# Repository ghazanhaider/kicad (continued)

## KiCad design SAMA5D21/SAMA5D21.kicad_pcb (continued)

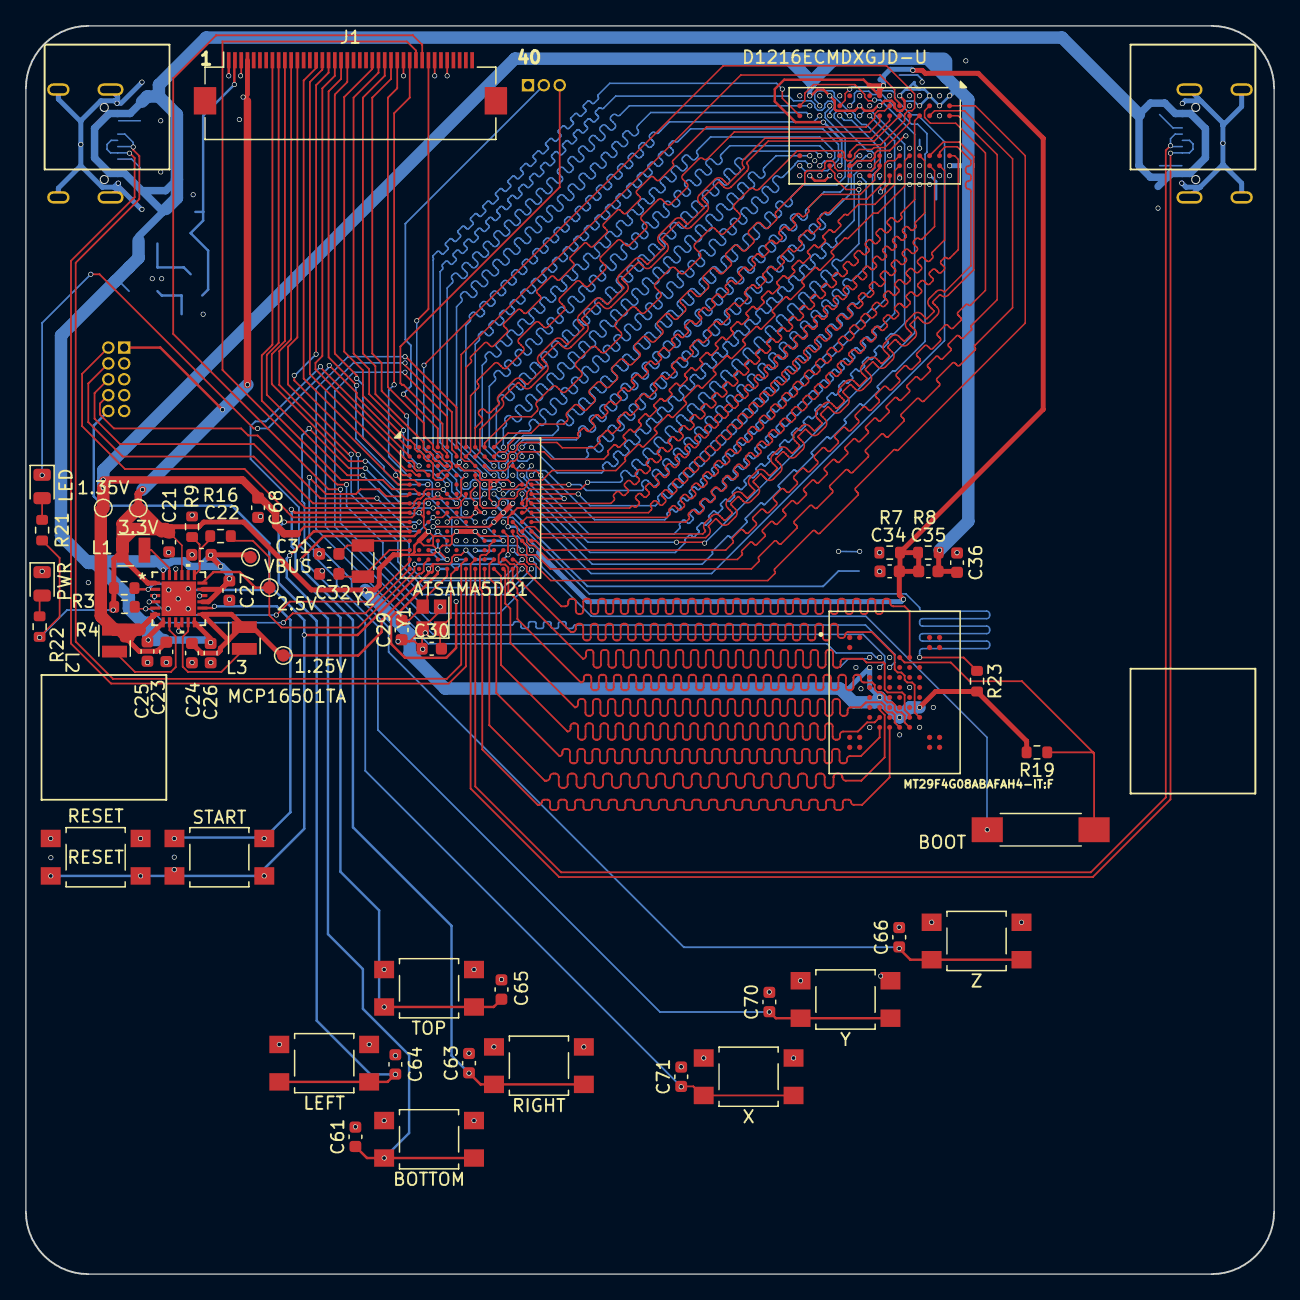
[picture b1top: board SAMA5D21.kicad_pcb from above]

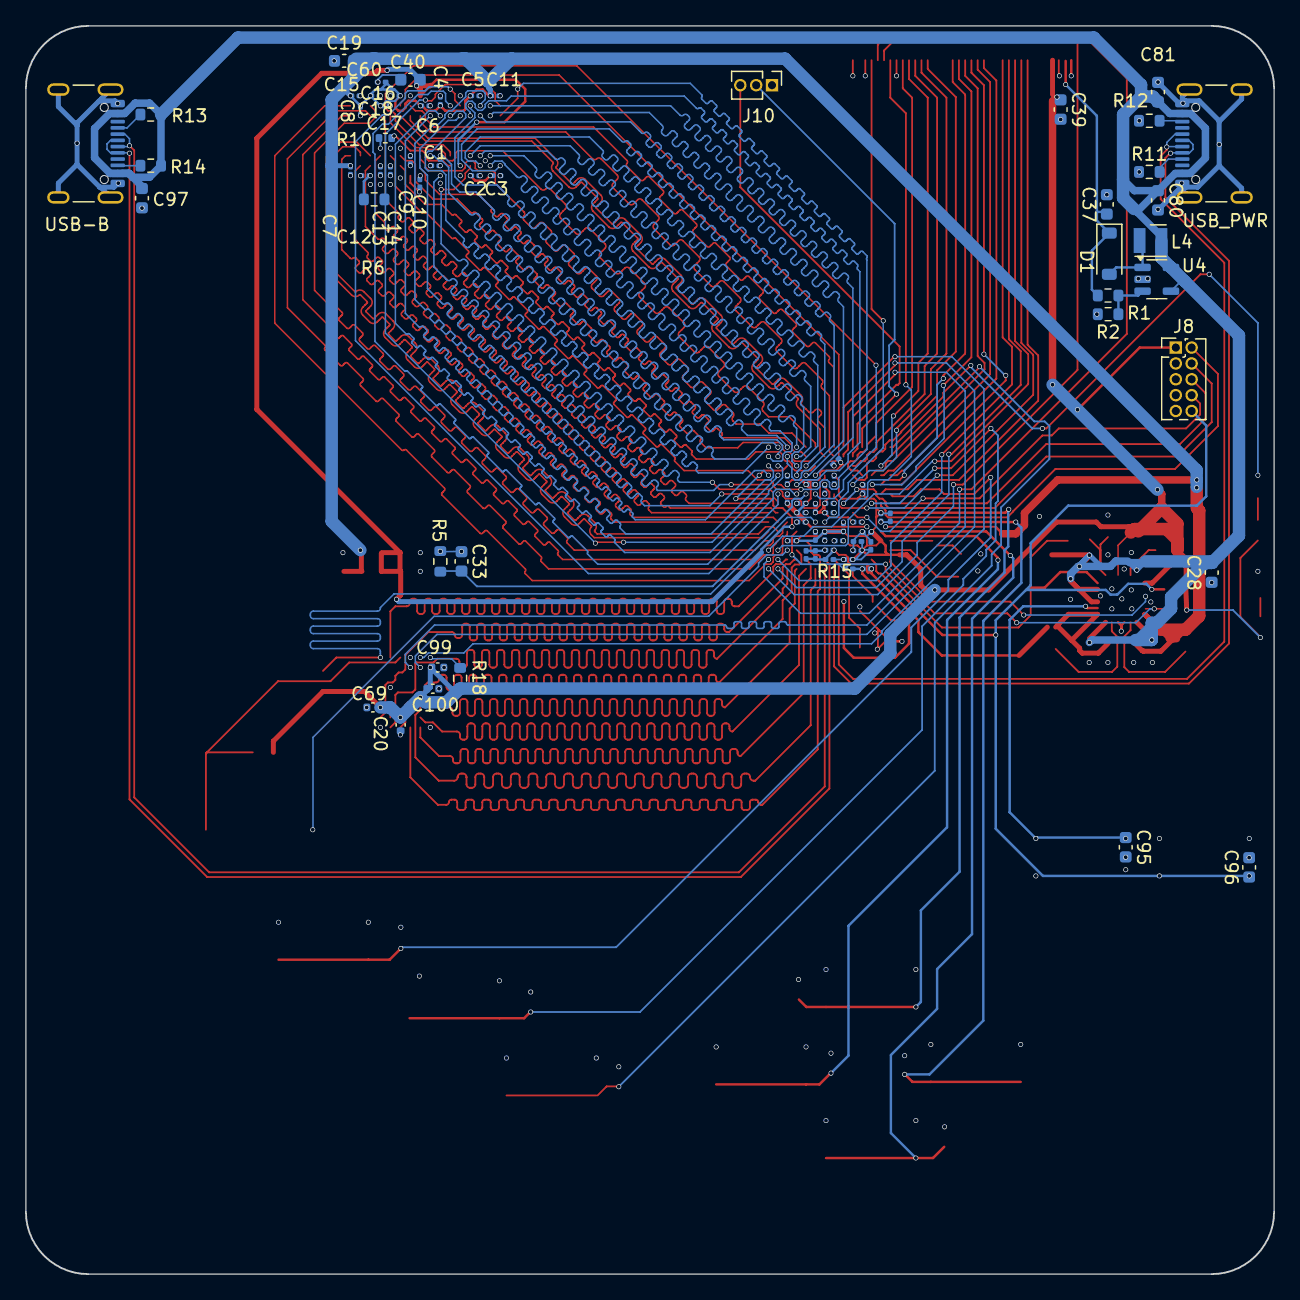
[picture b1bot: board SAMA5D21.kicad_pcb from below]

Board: 4 copper layers, 100.0 x 100.0 mm, 142 parts (83 on the bottom side), 132 nets.

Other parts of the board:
C20, C69, C99, C100: 100nF; C_0402_1005Metric
J8: SWD; PinHeader_2x05_P1.27mm_Vertical
JP1: BOOT; SW_SPST_REED_CT05-XXXX-G1
R18, R19: 470k; R_0603_1608Metric
R23: 1k; R_0603_1608Metric
U3: MT29F4G08ABAFAH4-IT:F; BGA63C80P10X12_1050X1300X100N

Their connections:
+3V3: C20.2, C69.2, C99.2, C100.2, J8.1 (VTref), R18.1, R19.2, R23.2, U3.D3 (VCC), U3.G4 (VCC), U3.H8 (VCC), U3.J6 (VCC); also elsewhere on the board
/NAND/NAND_CE: JP1.2 (B), R19.1, U3.C6 (CE#)
GNDADIOPLL: C20.1, C69.1, C99.1, C100.1, J8.3 (GND), J8.5 (GND), J8.9 (GNDDetect), U3.C5 (VSS), U3.F7 (VSS), U3.K3 (VSS), U3.K8 (VSS); also elsewhere on the board
JTAG_TCK: J8.4 (SWCLK/TCK); also elsewhere on the board
JTAG_TDI: J8.8 (TX/TDI); also elsewhere on the board
JTAG_TDO: J8.6 (SWO/TDO); also elsewhere on the board
JTAG_TMS: J8.2 (SWDIO/TMS); also elsewhere on the board
NANDALE: U3.C4 (ALE); also elsewhere on the board
NANDCLE: U3.D5 (CLE); also elsewhere on the board
NANDCS3: JP1.1 (A); also elsewhere on the board
NANDOE: U3.D4 (RE#); also elsewhere on the board
NANDRDY: R23.1, U3.C8 (R/B#); also elsewhere on the board
NANDWE: U3.C7 (WE#); also elsewhere on the board
NAND_D0: U3.H4 (I/O0); also elsewhere on the board
NAND_D1: U3.J4 (I/O1); also elsewhere on the board
NAND_D2: U3.K4 (I/O2); also elsewhere on the board
NAND_D3: U3.K5 (I/O3); also elsewhere on the board
NAND_D4: U3.K6 (I/O4); also elsewhere on the board
NAND_D5: U3.J7 (I/O5); also elsewhere on the board
NAND_D6: U3.K7 (I/O6); also elsewhere on the board
NAND_D7: U3.J8 (I/O7); also elsewhere on the board
NRST: J8.10 (~RESET); also elsewhere on the board
unnamed: R18.2, U3.C3 (WP#)

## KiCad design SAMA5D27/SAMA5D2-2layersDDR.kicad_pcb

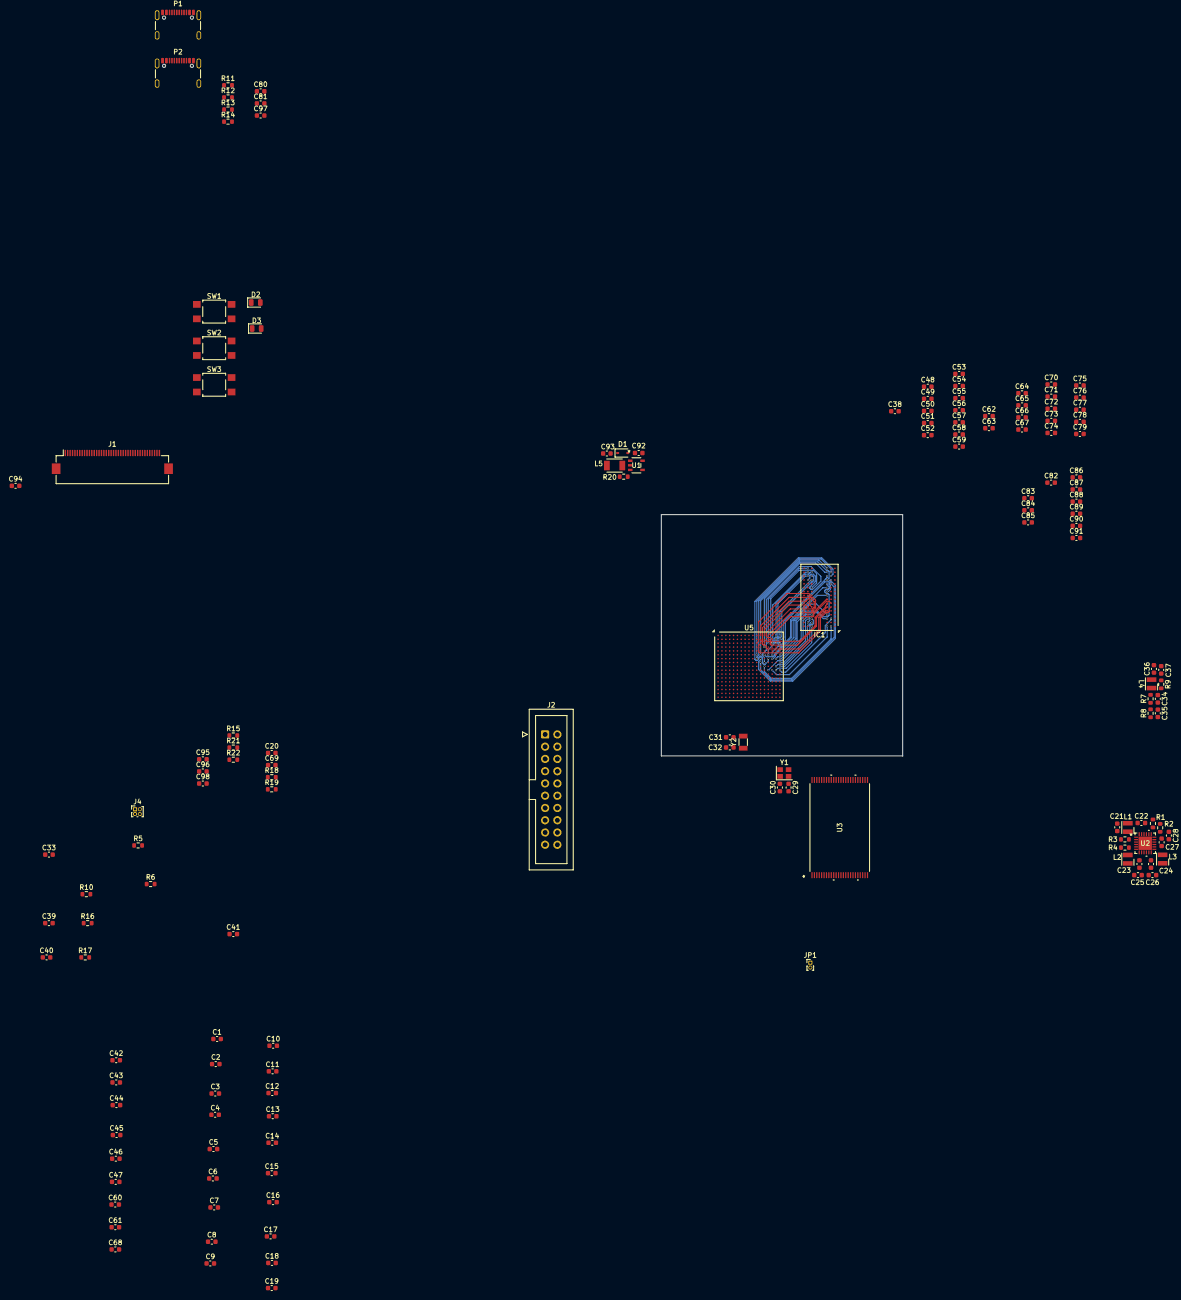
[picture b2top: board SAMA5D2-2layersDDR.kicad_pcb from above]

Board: 6 copper layers, 144 parts (0 on the bottom side), 143 nets.

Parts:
C1, C2, C3, C4, C5, C6, C7, C8, C9, C10, C11, C12, C13, C14, C15, C16, C17, C18, C20, C34, C35, C39, C40, C41, C42, C43, C44, C45, C46, C47, C48, C49, C50, C51, C52, C53, C54, C55, C57, C58, C62, C63, C65, C67, C69, C71, C72, C74, C76, C78, C79, C83, C87, C89, C91, C95, C96, C98: 100nF; C_0603_1608Metric
C19, C56, C59, C64, C66, C68, C70, C73, C75, C77, C82, C84, C85, C86, C88, C90, C92, C93: 1uF; C_0603_1608Metric
C21, C23, C24: 22uF; C_0603_1608Metric
C22, C25, C26, C27, C28, C36, C37, C80, C81, C94, C97: 4.7uF; C_0603_1608Metric
C29, C30, C31, C32: 16pF; C_0603_1608Metric
C33: 22pF; C_0603_1608Metric
C38: 10pF; C_0603_1608Metric
C60, C61: 10nF; C_0603_1608Metric
D1: D_Schottky; D_SOD-323
D2: USER_LED; LED_0805_2012Metric
D3: PWR_LED; LED_0805_2012Metric
IC1: D1216ECMDXGJD-U; Micron_FBGA-96_7.5x13.5mm_Layout9x16_P0.8mm
J1: LCD FPC 40pin; Hirose_FH12-40S-0.5SH_1x40-1MP_P0.50mm_Horizontal
J2: JTAG; IDC-Header_2x10_P2.54mm_Vertical
J4: UART1 Jumpers; PinHeader_2x02_P1.00mm_Vertical
JP1: NANDBOOT; PinHeader_1x02_P1.00mm_Vertical
L1, L2, L3: 2.2uH; L_Wurth_WE-LQSH-2512
L4: 10uH 150mA; L_Wurth_WE-LQSH-2512
L5: 15uH; L_TDK_NLV32_3.2x2.5mm
P1, P2: USB_C_Plug_USB2.0; USB_C_Receptacle_GCT_USB4105-xx-A_16P_TopMnt_Horizontal
R1: 182k 1%; R_0603_1608Metric
R2: 324k 1%; R_0603_1608Metric
R3, R4, R6: 100k; R_0603_1608Metric
R5: 23.2k 1%; R_0603_1608Metric
R7, R8: 6.8k 1%; R_0603_1608Metric
R9: 1R 1%; R_0603_1608Metric
R10: 240R 1%; R_0603_1608Metric
R11, R12: 5.1k 1%; R_0603_1608Metric
R13, R14: 56k 1%; R_0603_1608Metric
R15: 5.62k 1%; R_0603_1608Metric
R16: DNP; R_0603_1608Metric
R17: 0R; R_0603_1608Metric
R18, R19: 470k; R_0603_1608Metric
R20: 6.3; R_0603_1608Metric
R21, R22: 1k; R_0603_1608Metric
SW1: USER_BUTTON; SW_SPST_TL3305A
SW2: START; SW_SPST_TL3305A
SW3: RESET; SW_SPST_TL3305A
U1: MIC2287CYD5-TR; TSOT-23-5_D5_MCH
U2: MCP16501TA-E/RMB; VQFN24_RMB_MCH
U3: MT29F4G08ABAEAWP-IT:E TR; TSOPI-48_MRN
U5: ATSAMA5D27C-CU; LFBGA-289_14x14mm_Layout17x17_P0.8mm
Y1: 12MHz XTAL; Crystal_SMD_2520-4Pin_2.5x2.0mm
Y2: 32.768kHz; Crystal_SMD_3215-2Pin_3.2x1.5mm

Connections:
+1V25: C24.2, C48.1, C49.1, C50.1, C51.1, C52.1, C53.1, C62.2, C64.2, C71.1, C72.1, C73.1, C82.1, C84.1, L3.1, U2.13 (OUT3), U5.D7 (VDDCORE), U5.D9 (VDDCORE), U5.H3 (VDDCORE), U5.K13 (VDDCORE), U5.N5 (VDDCORE), U5.N9 (VDDCORE), U5.P7 (VDDUTMIC), U5.R9 (VDDHSIC), U5.U4 (VDDPLLA)
+2V5: C28.1, C89.1, C90.1, R2.2, U2.18 (LOUT), U5.M12 (VDDFUSE)
+3V3: C20.2, C21.1, C54.1, C55.1, C56.1, C57.1, C58.1, C59.1, C63.1, C65.2, C66.2, C67.2, C69.2, C70.2, C74.1, C75.1, C76.1, C77.1, C78.1, C79.1, C83.1, C85.1, C86.1, C87.1, C88.1, C91.2, C94.2, J1.4, J2.1 (VTREF), J2.2 (VCC/NC), L1.2, R3.2, R4.2, R18.1, R19.2, R21.1, R22.1, U2.1 (OUT1), U2.21 (LEN), U3.12 (VCC), U3.37 (VCC), U5.E6 (VDDIOP0), U5.F4 (VDDISC), U5.F7 (VDDIOP0), U5.F10 (VDDIOP2), U5.K3 (VDDANA), U5.L5 (VDDANA), U5.M6 (ADVREFP), U5.N7 (VDDBU), U5.N13 (VDDIOP1), U5.P8 (VDDUTMII), U5.P11 (VDDSDMMC), U5.R14 (VDDIOP1), U5.T3 (VDDAUDIOPLL), U5.T7 (VDDOSC)
A0: IC1.N3 (A0), U5.F12 (DDR_A0)
A1: IC1.P7 (A1), U5.C17 (DDR_A1)
A2: IC1.P3 (A2), U5.B17 (DDR_A2)
A3: IC1.N2 (A3), U5.B16 (DDR_A3)
A4: IC1.P8 (A4), U5.C16 (DDR_A4)
A5: IC1.P2 (A5), U5.G14 (DDR_A5)
A6: IC1.R8 (A6), U5.F14 (DDR_A6)
A7: IC1.R2 (A7), U5.F11 (DDR_A7)
A8: IC1.T8 (A8), U5.C14 (DDR_A8)
A9: IC1.R3 (A9), U5.D13 (DDR_A9)
A10: IC1.L7 (A10/AP), U5.C15 (DDR_A10)
A11: IC1.R7 (A11), U5.A16 (DDR_A11)
A12: IC1.N7 (A12/BC#), U5.A17 (DDR_A12)
A13: IC1.T3 (A13), U5.G11 (DDR_A13)
BA0: IC1.M2 (BA0), U5.H12 (DDR_BA0)
BA1: IC1.N8 (BA1), U5.H13 (DDR_BA1)
BA2: IC1.M3 (BA2), U5.F17 (DDR_BA2)
CASn: IC1.K3 (CAS#), U5.G12 (DDR_CAS)
CK: IC1.J7 (CK), U5.E17 (DDR_CLK)
CKE: IC1.K9 (CKE), U5.F16 (DDR_CKE)
CKn: IC1.K7 (CK#), U5.D17 (DDR_CLKN)
CSn: IC1.L2 (CS#), U5.G13 (DDR_CS)
DDR_CAL: C33.1, R5.2, U5.E13 (DDR_CAL)
DDR_D0: IC1.E3 (DQL0), U5.B12 (DDR_D0)
DDR_D1: IC1.F7 (DQL1), U5.A12 (DDR_D1)
DDR_D2: IC1.F2 (DQL2), U5.C12 (DDR_D2)
DDR_D3: IC1.F8 (DQL3), U5.A13 (DDR_D3)
DDR_D4: IC1.H3 (DQL4), U5.A14 (DDR_D4)
DDR_D5: IC1.H8 (DQL5), U5.C13 (DDR_D5)
DDR_D6: IC1.G2 (DQL6), U5.A15 (DDR_D6)
DDR_D7: IC1.H7 (DQL7), U5.B15 (DDR_D7)
DDR_D8: IC1.D7 (DQU0), U5.G17 (DDR_D8)
DDR_D9: IC1.C3 (DQU1), U5.G16 (DDR_D9)
DDR_D10: IC1.C8 (DQU2), U5.H17 (DDR_D10)
DDR_D11: IC1.C2 (DQU3), U5.K17 (DDR_D11)
DDR_D12: IC1.A7 (DQU4), U5.K16 (DDR_D12)
DDR_D13: IC1.A2 (DQU5), U5.J13 (DDR_D13)
DDR_D14: IC1.B8 (DQU6), U5.K14 (DDR_D14)
DDR_D15: IC1.A3 (DQU7), U5.K15 (DDR_D15)
DDR_DQM0: IC1.E7 (DML), U5.C11 (DDR_DQM0)
DDR_DQM1: IC1.D3 (DMU), U5.G15 (DDR_DQM1)
DDR_DQS0: IC1.F3 (DQSL), U5.B13 (DDR_DQS0)
DDR_DQS1: IC1.C7 (DQSU), U5.J17 (DDR_DQS1)
DDR_DQSN0: IC1.G3 (DQSL#), U5.B14 (DDR_DQSN0)
DDR_DQSN1: IC1.B7 (DQSU#), U5.J16 (DDR_DQSN1)
DDR_RAS: IC1.J3 (RAS#), U5.F13 (DDR_RAS)
DDR_RESETN: IC1.T2 (RESET#), R6.1, U5.E16 (DDR_RESETN)
DDR_VREF: C34.2, C35.1, R7.1, R8.2, U5.D16 (DDR_VREF), U5.H16 (DDR_VREF)
DDR_WE: IC1.L3 (WE#), U5.F15 (DDR_WE)
GND: C1.1, C2.1, C3.1, C4.1, C5.1, C6.1, C7.1, C8.1, C9.1, C10.1, C11.1, C12.1, C13.1, C14.1, C15.1, C16.1, C17.1, C18.1, C19.1, C20.1, C21.2, C22.2, C23.2, C24.1, C25.2, C26.1, C27.2, C28.2, C29.1, C30.1, C31.2, C32.2, C33.2, C35.2, C36.2, C37.2, C39.2, C40.2, C41.2, C42.2, C43.2, C44.2, C45.2, C46.2, C47.2, C48.2, C49.2, C50.2, C51.2, C52.2, C53.2, C54.2, C55.2, C56.2, C57.2, C58.2, C59.2, C60.2, C61.2, C63.2, C67.1, C68.2, C69.1, C70.1, C71.2, C72.2, C73.2, C74.2, C75.2, C76.2, C77.2, C78.2, C79.2, C80.2, C81.2, C82.2, C83.2, C84.2, C85.2, C86.2, C87.2, C88.2, C89.2, C90.2, C91.1, C92.2, C93.2, C94.1, C95.2, C96.2, C97.2, C98.2, D3.1 (K), IC1.A9 (VSS_1), IC1.B1 (VSSQ_1), IC1.B3 (VSS_2), IC1.B9 (VSSQ_2), IC1.D1 (VSSQ_3), IC1.D8 (VSSQ_4), IC1.E1 (VSS_3), IC1.E2 (VSSQ_5), IC1.E8 (VSSQ_6), IC1.F9 (VSSQ_7), IC1.G1 (VSSQ_8), IC1.G8 (VSS_4), IC1.G9 (VSSQ_9), IC1.J2 (VSS_5), IC1.J8 (VSS_6), IC1.M1 (VSS_7), IC1.M9 (VSS_8), IC1.P1 (VSS_9), IC1.P9 (VSS_10), IC1.T1 (VSS_11), IC1.T9 (VSS_12), J1.3, J1.29, J1.36, J2.4 (GND), J2.6 (GND), J2.8 (GND), J2.10 (GND), J2.12 (GND), J2.14 (GND), J2.16 (GND), J2.18 (GND), J2.20 (GND), P1.A1 (GND), P1.A12 (GND), P1.B1 (GND), P1.B12 (GND), P1.S1 (SHIELD), P2.A1 (GND), P2.A12 (GND), P2.B1 (GND), P2.B12 (GND), P2.S1 (SHIELD), R1.2, R5.1, R8.1, R10.2, R11.1, R12.1, R17.2, R20.2, SW1.1, SW2.1, SW3.1, U1.2 (GND), U2.4 (LPM), U2.9 (PGND2), U2.10 (PGND3), U2.16 (SGND), U2.22 (PGND1), U2.25 (GND), U3.13 (VSS), U3.36 (VSS), U3.38 (PRE/VSS), U5.D14 (GNDIODDR), U5.E11 (GNDIODDR), U5.E12 (GNDIODDR), U5.E14 (GNDIODDR), U5.H14 (GNDIODDR), U5.J14 (GNDIODDR), U5.L14 (GNDIODDR), U5.P3 (TST), Y1.2, Y1.4
GNDANA: U5.K5 (GNDANA), U5.L3 (GNDANA)
GNDCORE: U5.E7 (GNDCORE), U5.E9 (GNDCORE), U5.H4 (GNDCORE), U5.K12 (GNDCORE), U5.M5 (GNDCORE), U5.M9 (GNDCORE)
GNDIOP0: U5.F6 (GNDIOP0), U5.G7 (GNDIOP0)
GNDIOP1: U5.M13 (GNDIOP1), U5.P14 (GNDIOP1)
GNDUTMIC: C62.1, C64.1, U5.R7 (GNDUTMIC)
GNDUTMII: C38.2, C65.1, C66.1, R15.1, U5.P9 (GNDUTMII)
HHSDMA: P1.A7 (D-), U5.R8 (HHSDMA)
HHSDMB: P2.A7 (D-), U5.U9 (HHSDMB)
HHSDPA: P1.A6 (D+), U5.T8 (HHSDPA)
HHSDPB: P2.A6 (D+), U5.U8 (HHSDPB)
JTAG_NTRST: J2.3 (~TRST), U5.J5 (PD18)
JTAG_TCK: J2.9 (TCK/SWCLK), U5.K4 (PD14)
JTAG_TDI: J2.5 (TDI), J4.1, U5.K7 (PD15)
JTAG_TDO: J2.13 (TDO/SWO), U5.L1 (PD16)
JTAG_TMS: J2.7 (TMS/SWDIO), U5.K2 (PD17)
LCDDAT2: J1.7, U5.E3 (PC10)
LCDDAT3: J1.8, U5.E2 (PC11)
LCDDAT4: J1.9, U5.E1 (PC12)
LCDDAT5: J1.10, U5.F3 (PC13)
LCDDAT6: J1.11, U5.F5 (PC14)
LCDDAT7: J1.12, U5.F2 (PC15)
LCDDAT10: J1.15, U5.G6 (PC16)
LCDDAT11: J1.16, U5.F1 (PC17)
LCDDAT12: J1.17, U5.H6 (PC18)
LCDDAT13: J1.18, U5.G2 (PC19)
LCDDAT14: J1.19, U5.G3 (PC20)
LCDDAT15: J1.20, U5.G1 (PC21)
LCDDAT18: J1.23, U5.H2 (PC22)
LCDDAT19: J1.24, U5.G5 (PC23)
LCDDAT20: J1.25, U5.H1 (PC24)
LCDDAT21: J1.26, U5.H5 (PC25)
LCDDAT22: J1.27, U5.J9 (PC26)
LCDDAT23: J1.28, U5.H9 (PC27)
LCDDEN: J1.34, U5.E10 (PD1)
LCDDISP: J1.31, U5.G8 (PC29)
LCDHSYNC: J1.32, U5.D8 (PC31)
LCDPCK: J1.30, U5.G10 (PD0)
LCDPWM: U1.4 (EN), U5.E8 (PC28)
LCDVSYNC: J1.33, U5.F8 (PC30)
NANDALE: U3.17 (ALE), U5.J8 (PB0)
NANDCLE: U3.16 (CLE), U5.A8 (PB1)
NANDCS3: JP1.1 (A), U5.R17 (PA31)
NANDOE: U3.8 (RE#), U5.A7 (PB2)
NANDRDY: U3.7 (R/B#), U5.J10 (PC8)
NANDWE: U3.18 (WE#), U5.R15 (PA30)
NAND_D0: U3.29 (I/O0), U5.U15 (PA22)
NAND_D1: U3.30 (I/O1), U5.U16 (PA23)
NAND_D2: U3.31 (I/O2), U5.T15 (PA24)
NAND_D3: U3.32 (I/O3), U5.U17 (PA25)
NAND_D4: U3.41 (I/O4), U5.P13 (PA26)
NAND_D5: U3.42 (I/O5), U5.T16 (PA27)
NAND_D6: U3.43 (I/O6), U5.R16 (PA28)
NAND_D7: U3.44 (I/O7), U5.T17 (PA29)
NRST: C96.1, J2.15 (~SRST), R3.1, SW3.2, U2.2 (nRSTO), U5.U2 (NRST)
unnamed: C34.1, L4.2, R7.2, R9.1
unnamed: C37.1, R9.2
unnamed: D1.2 (A), L5.2, U1.1 (SW)
unnamed: C93.1, D1.1 (K), J1.2
unnamed: D2.2 (A), R21.2
unnamed: D3.2 (A), R22.2
unnamed: IC1.K1 (ODT), R16.1, R17.1
unnamed: IC1.L8 (ZQ), R10.1
unnamed: J1.1, R20.1, U1.3 (FB)
unnamed: J2.17 (DBGRQ/NC), J4.3
unnamed: JP1.2 (B), R19.1, U3.9 (CE#)
unnamed: P1.A5 (CC), R11.2
unnamed: P1.B5 (VCONN), R12.2
unnamed: P2.A5 (CC), R13.2
unnamed: P2.B5 (VCONN), R14.2
unnamed: R1.1, R2.1, U2.19 (LFB)
unnamed: L1.1, U2.23 (SW1)
unnamed: L2.2, U2.8 (SW2)
unnamed: L3.2, U2.11 (SW3)
unnamed: R18.2, U3.19 (WP#)
PD2: J4.2, U5.G9 (PD2)
PD3: J4.4, U5.K1 (PD3)
PD19: D2.1 (K), U5.K6 (PD19)
PD20: C98.1, SW1.2, U5.M2 (PD20)
SHDN: U2.3 (PWRHLD), U5.R1 (SHDN)
START: C95.1, SW2.2, U2.14 (nSTRT)
VBG: C38.1, R15.2, U5.R6 (VBG)
VBUS: C22.1, C25.1, C26.2, C27.1, C80.1, C81.1, C92.1, C97.1, L5.1, P1.A4 (VBUS), P1.A9 (VBUS), P1.B4 (VBUS), P1.B9 (VBUS), P2.A4 (VBUS), P2.A9 (VBUS), P2.B4 (VBUS), P2.B9 (VBUS), R13.1, R14.1, U1.5 (VIN), U2.7 (PVIN2), U2.12 (PVIN3), U2.15 (SELV3), U2.17 (VIN), U2.24 (PVIN1)
VDDIODDR: C1.2, C2.2, C3.2, C4.2, C5.2, C6.2, C7.2, C8.2, C9.2, C10.2, C11.2, C12.2, C13.2, C14.2, C15.2, C16.2, C17.2, C18.2, C19.2, C23.1, C36.1, C41.1, C42.1, C43.1, C44.1, C45.1, C46.1, C47.1, C60.1, C61.1, C68.1, IC1.A1 (VDDQ_1), IC1.A8 (VDDQ_2), IC1.B2 (VDD_1), IC1.C1 (VDDQ_3), IC1.C9 (VDDQ_4), IC1.D2 (VDDQ_5), IC1.D9 (VDD_2), IC1.E9 (VDDQ_6), IC1.F1 (VDDQ_7), IC1.G7 (VDD_3), IC1.H2 (VDDQ_8), IC1.H9 (VDDQ_9), IC1.K2 (VDD_4), IC1.K8 (VDD_5), IC1.N1 (VDD_6), IC1.N9 (VDD_7), IC1.R1 (VDD_8), IC1.R9 (VDD_9), L2.1, L4.1, R6.2, R16.2, U2.6 (OUT2), U5.D11 (VDDIODDR), U5.D12 (VDDIODDR), U5.D15 (VDDIODDR), U5.E15 (VDDIODDR), U5.H15 (VDDIODDR), U5.J15 (VDDIODDR), U5.L15 (VDDIODDR)
VREFCA: C40.1, IC1.M8 (VREFCA)
VREFDQ: C39.1, IC1.H1 (VREFDQ)
WKUP: R4.1, U2.5 (nSTRTO), U5.P4 (WKUP)
XIN: C29.2, U5.U7 (XIN), Y1.3
XIN32: C32.1, U5.P1 (XIN32), Y2.2
XOUT: C30.2, U5.U6 (XOUT), Y1.1
XOUT32: C31.1, U5.P2 (XOUT32), Y2.1

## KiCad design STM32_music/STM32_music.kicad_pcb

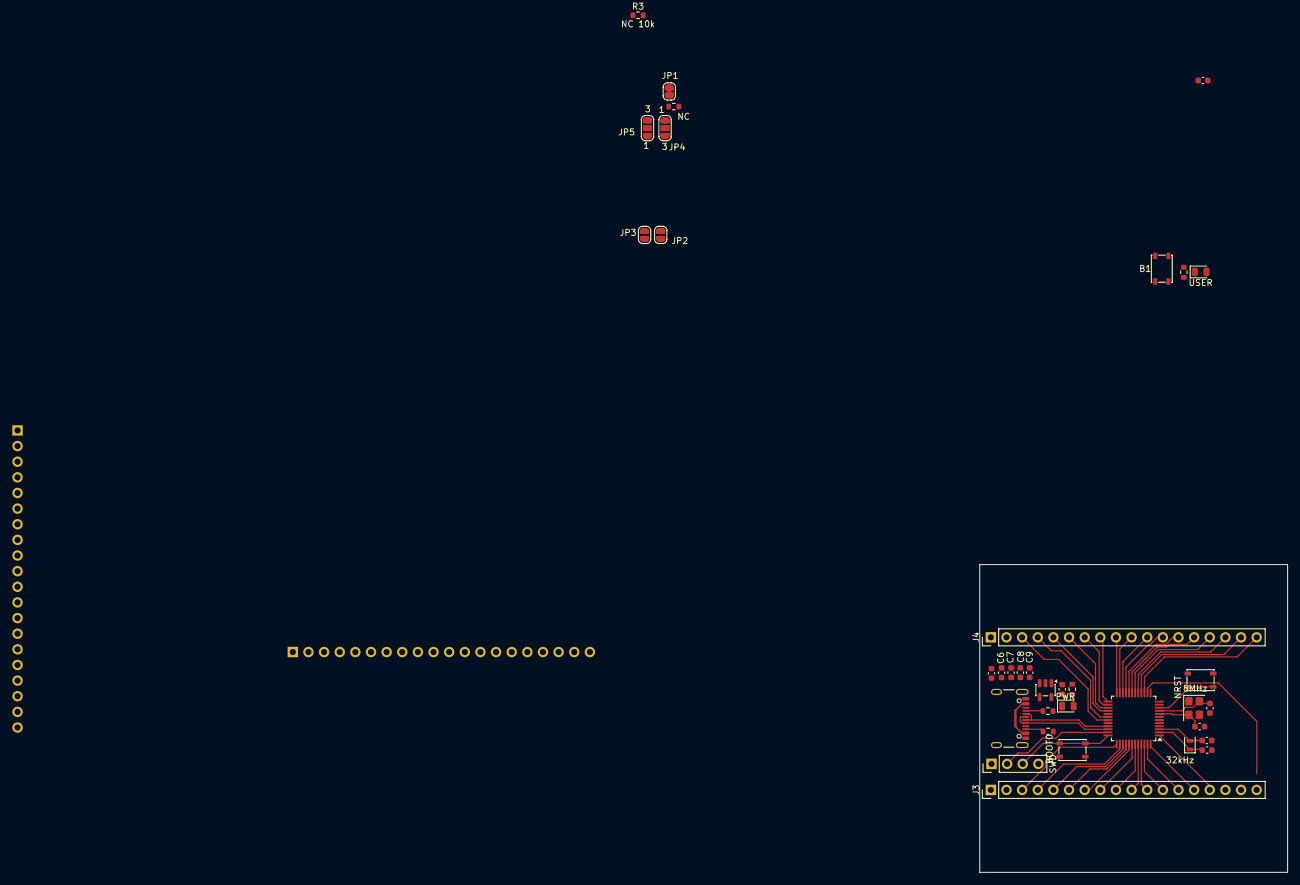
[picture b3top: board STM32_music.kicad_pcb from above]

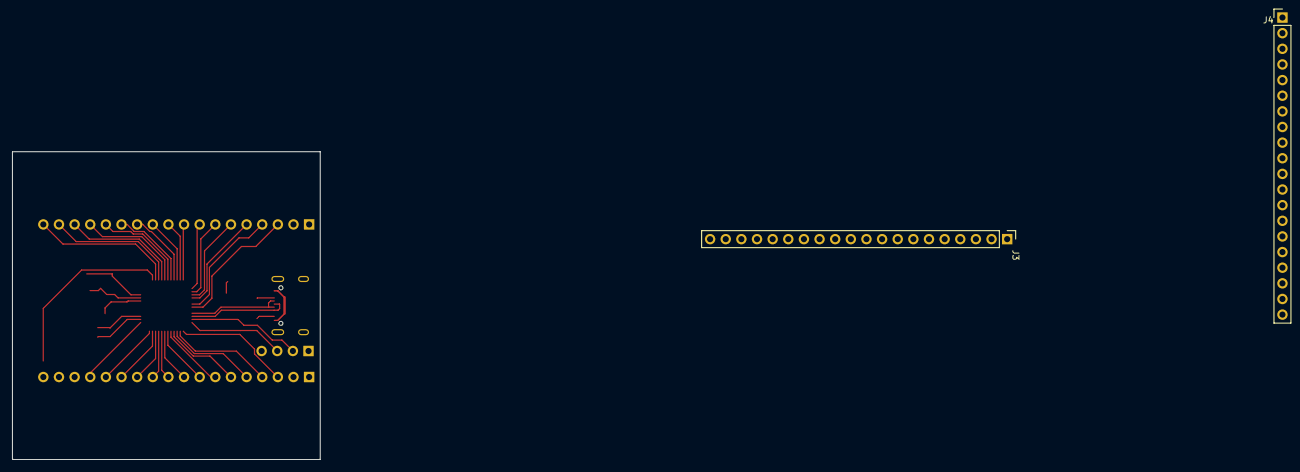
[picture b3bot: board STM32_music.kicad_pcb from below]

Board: 2 copper layers, 50.0 x 50.0 mm, 37 parts (2 on the bottom side), 55 nets.

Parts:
C1, C6, C7, C8, C9: 0.1uF; C_0603_1608Metric
C2, C3: 18 pF; C_0603_1608Metric
C4, C5: 30pF; C_0603_1608Metric
C10, C11: 1uF; C_0603_1608Metric
D1: PWR; LED_0805_2012Metric
D2: USER; LED_0805_2012Metric
J1: USB_C_Receptacle_USB2.0_14P; USB_C_Receptacle_GCT_USB4105-xx-A_16P_TopMnt_Horizontal
J2: SWD; PinHeader_1x04_P2.54mm_Vertical
J3: P1; PinHeader_1x18_P2.54mm_Vertical
J3#2: P1; PinHeader_1x20_P2.54mm_Vertical
J4: P2; PinHeader_1x18_P2.54mm_Vertical
J4#2: P2; PinHeader_1x20_P2.54mm_Vertical
JP1: VBAT; SolderJumper-2_P1.3mm_Bridged_RoundedPad1.0x1.5mm
JP2: CC1; SolderJumper-2_P1.3mm_Open_RoundedPad1.0x1.5mm
JP3: CC2; SolderJumper-2_P1.3mm_Open_RoundedPad1.0x1.5mm
JP4, JP5: SolderJumper_3_Open; SolderJumper-3_P1.3mm_Open_RoundedPad1.0x1.5mm_NumberLabels
R1: NC; R_0603_1608Metric
R2, R6: 1k; R_0603_1608Metric
R3: NC 10k; R_0603_1608Metric
R4, R5: 5.1k; R_0603_1608Metric
SW1: NRST; SW_SPST_PTS810
SW2: BOOT0; SW_SPST_PTS810
SW3: B1; SW_SPST_PTS810
U1: STM32G0B0CETx; LQFP-48_7x7mm_P0.5mm
U2: RT9701; SOT-23-5
Y1: 32kHz; Crystal_SMD_2012-2Pin_2.0x1.2mm
Y2: 8MHz; Crystal_SMD_3225-4Pin_3.2x2.5mm

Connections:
+3.3V: C6.1, C7.1, C8.1, C9.1, C11.1, J2.1, J3#2.3, J4.1, J4#2.20, JP1.2 (B), R1.1, R6.2, SW2.2 (B), U1.5 (VREF+), U1.6 (VDD), U2.1 (VOUT), U2.5 (VOUT)
+5V: C10.1, J1.A4 (VBUS), J1.A9 (VBUS), J1.B4 (VBUS), J1.B9 (VBUS), J3.1, J3#2.1, J4#2.18, U2.3 (VIN), U2.4 (VIN/EN)
BOOT0/SWCLK: J2.3, R3.1, SW2.1 (A), U1.36 (PA14)
CC1: J1.A5 (CC1), JP2.1 (A), R4.1
CC2: J1.B5 (CC2), JP3.1 (A), R5.2
GND: C1.1, C2.1, C3.1, C4.1, C5.1, C6.2, C7.2, C8.2, C9.2, C10.2, C11.2, D1.1 (K), J1.A1 (GND), J1.A12 (GND), J1.B1 (GND), J1.B12 (GND), J1.S1 (SHIELD), J2.4, J3.2, J3#2.2, J4.2, J4#2.19, R2.2, R3.2, R4.2, R5.1, SW1.1 (A), SW3.2 (B), U1.7 (VSS), U2.2 (GND), Y2.3
NRST: C1.2, J3#2.16, R1.2, SW1.2 (B), U1.10 (NRST)
unnamed: D1.2 (A), R6.1
unnamed: D2.1 (K), R2.1
unnamed: JP2.2 (B), JP4.2 (C)
unnamed: JP3.2 (B), JP5.2 (C)
unnamed: C2.2, U1.2 (PC14), Y1.1
unnamed: C3.2, U1.3 (PC15), Y1.2
unnamed: C4.2, U1.8 (PF0), Y2.2
unnamed: C5.2, U1.9 (PF1), Y2.1
PA0: J3#2.15, SW3.1 (A), U1.11 (PA0)
PA1: J3#2.14, U1.12 (PA1)
PA2: J3#2.13, U1.13 (PA2)
PA3: J3#2.12, U1.14 (PA3)
PA4: J3#2.11, J4.18, U1.15 (PA4)
PA5: J3#2.10, J4.17, U1.16 (PA5)
PA6: J3#2.9, J4.16, U1.17 (PA6)
PA7: J3#2.8, J4.15, U1.18 (PA7)
PA8: J4.5, J4#2.5, U1.28 (PA8)
PA15: J3.3, J4#2.10, U1.37 (PA15)
PB0: J3#2.7, J4.14, U1.19 (PB0)
PB1: J3#2.6, J4.13, U1.20 (PB1)
PB2: J3#2.5, J4.12, U1.21 (PB2)
PB3: J3.8, J4#2.11, U1.42 (PB3)
PB4: J3.9, J4#2.12, U1.43 (PB4)
PB5: J3.10, J4#2.13, U1.44 (PB5)
PB6: J3.11, J4#2.14, U1.45 (PB6)
PB7: J3.12, J4#2.15, U1.46 (PB7)
PB8: J3.13, J4#2.16, U1.47 (PB8)
PB9: J3.14, J4#2.17, U1.48 (PB9)
PB10: J3#2.4, J4.11, U1.22 (PB10)
PB11: J4.10, J4#2.6, U1.23 (PB11)
PB12: J4.9, J4#2.1, U1.24 (PB12)
PB13: J4.8, J4#2.2, U1.25 (PB13)
PB14: J4.7, J4#2.3, U1.26 (PB14)
PB15: J4.6, J4#2.4, U1.27 (PB15)
PC6: J4.4, J4#2.7, U1.30 (PC6)
PC7: J4.3, J4#2.8, U1.31 (PC7)
PC13: D2.2 (A), J3.15, J4#2.9, U1.1 (PC13)
PD0: J3.4, U1.38 (PD0)
PD1: J3.5, U1.39 (PD1)
PD2: J3.6, U1.40 (PD2)
PD3: J3.7, U1.41 (PD3)
SWDIO: J2.2, U1.35 (PA13)
UCPD2_CC1: J3#2.17, JP4.1 (A)
UCPD2_CC2: J3#2.19, JP5.1 (A)
UCPD2_DBCC2: J3#2.18, JP5.3 (B)
USB_DM: J1.A7 (D-), J1.B7 (D-), U1.33 (PA9/PA11)
USB_DP: J1.A6 (D+), J1.B6 (D+), U1.34 (PA10/PA12)
VBAT: J3#2.20, JP1.1 (A), U1.4 (VBAT)
